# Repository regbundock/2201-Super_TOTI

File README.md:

"# 2201-Super_TOTI" 
A single channel device with the following characteristics.
Powered from the DCC and has a small current drain of ~5mA, has an assured sensitivity of 10K and has a low input impedance of <200 Ohms

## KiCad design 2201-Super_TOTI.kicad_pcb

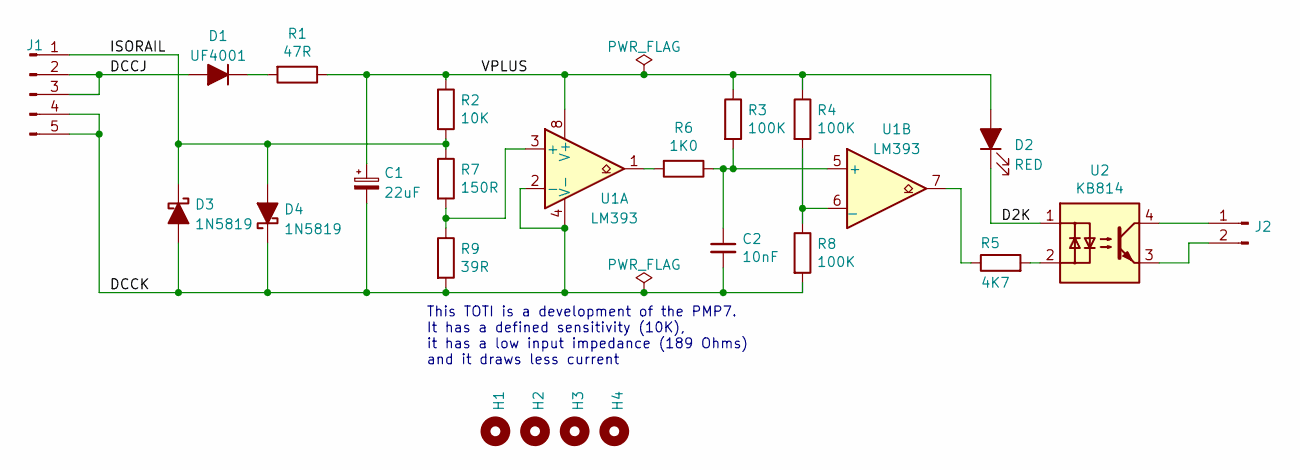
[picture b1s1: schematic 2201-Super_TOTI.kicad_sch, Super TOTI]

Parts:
C1: 22uF; CP_Radial_D6.3mm_P2.50mm
C2: 10nF; C_Disc_D4.3mm_W1.9mm_P5.00mm
D1: UF4001; D_DO-41_SOD81_P10.16mm_Horizontal
D2: RED; LED_D3.0mm
D3, D4: 1N5819; D_DO-41_SOD81_P10.16mm_Horizontal
H1, H2, H3, H4: MountingHole; MountingHole_2.7mm_M2.5
J1: Conn_01x05_Male; Molex_KK-396_5273-05A_1x05_P3.96mm_Vertical
J2: Conn_01x02_Male; Molex_KK-254_AE-6410-02A_1x02_P2.54mm_Vertical
R1: 47R; R_Axial_DIN0207_L6.3mm_D2.5mm_P10.16mm_Horizontal
R2: 10K; R_Axial_DIN0207_L6.3mm_D2.5mm_P10.16mm_Horizontal
R3, R4, R8: 100K; R_Axial_DIN0207_L6.3mm_D2.5mm_P10.16mm_Horizontal
R5: 4K7; R_Axial_DIN0207_L6.3mm_D2.5mm_P10.16mm_Horizontal
R6: 1K0; R_Axial_DIN0207_L6.3mm_D2.5mm_P10.16mm_Horizontal
R7: 150R; R_Axial_DIN0207_L6.3mm_D2.5mm_P10.16mm_Horizontal
R9: 39R; R_Axial_DIN0207_L6.3mm_D2.5mm_P10.16mm_Horizontal
U1: LM393; DIP-8_W7.62mm_Socket
U2: KB814; DIP-4_W7.62mm

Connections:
/D2K: D2.1 (K), U2.1
/DCCJ: D1.2 (A), J1.2, J1.3
/DCCK: C1.2, C2.2, D3.2 (A), D4.1 (K), J1.4, J1.5, R8.2, R9.2, U1.2 (-), U1.4 (V-)
/ISORAIL: D3.1 (K), D4.2 (A), J1.1, R2.2, R7.1
/VPLUS: C1.1, D2.2 (A), R1.1, R2.1, R3.1, R4.1, U1.8 (V+)
unnamed: C2.1, R3.2, R6.1, U1.5 (+)
unnamed: J2.1, U2.4
unnamed: J2.2, U2.3
unnamed: D1.1 (K), R1.2
unnamed: R4.2, R8.1, U1.6 (_)
unnamed: R6.2, U1.1
unnamed: R7.2, R9.1, U1.3 (+)
unnamed: R5.1, U1.7
unnamed: R5.2, U2.2

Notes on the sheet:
This TOTI is a development of the PMP7. It has a defined sensitivity (10K), it has a low input impedance (189 Ohms) and it draws less current

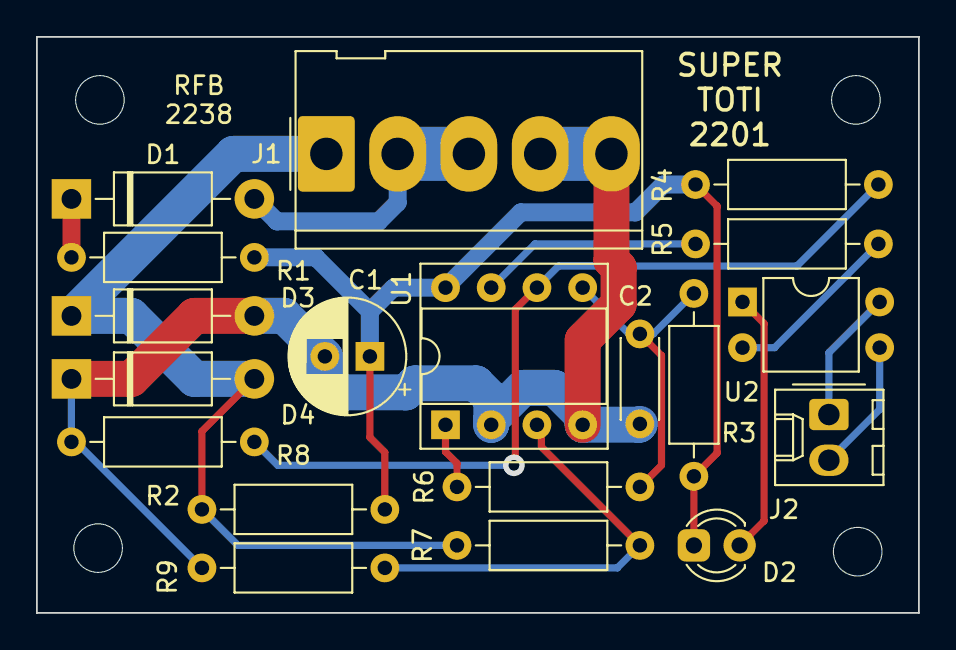
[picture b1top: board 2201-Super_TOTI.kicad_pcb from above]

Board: 2 copper layers, 49.0 x 32.0 mm, 23 parts (0 on the bottom side), 14 nets.
